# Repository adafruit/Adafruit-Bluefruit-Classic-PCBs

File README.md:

## Bluefruit EZ-Link - Bluetooth Serial Link & Arduino Programmer - v1.3 PCBs (Discontinued)
<a href="http://www.adafruit.com/products/1588"><br/>
Click here to view in the Adafruit shop</a>

The Bluefruit EZ-Link is a regular 'SPP' serial link client device, that can pair with any computer or tablet and appear as a serial/COM port (except iOS as iOS does not permit SPP pairing). But here is where it gets exciting: unlike any other BT module, the EZ-Link can automatically detect and change the serial baud rate. That means if you open up the COM port on your computer at 9600 baud, the output is 9600, 57600? 57600. Yep even 2400. All the most common baud rates are supported: 2400, 4800, 9600, 19200, 38400, 57600, 115200 and 230400. You never have to configure or customize the module by hand - it all happens completely automatically inside the RF module.

PCB files for the discontinued Adafruit Bluefruit Classic (2.1) EZ-Link. The PCB format is EagleCAD schematic and board layout
- https://www.adafruit.com/products/1588

### License

Adafruit invests time and resources providing this open source design, please support Adafruit and open-source hardware by purchasing products from [Adafruit](https://www.adafruit.com)!

All text above must be included in any redistribution

Designed by Limor Fried/Ladyada for Adafruit Industries.
Creative Commons Attribution/Share-Alike, all text above must be included in any redistribution. 
See license.txt for additional information.

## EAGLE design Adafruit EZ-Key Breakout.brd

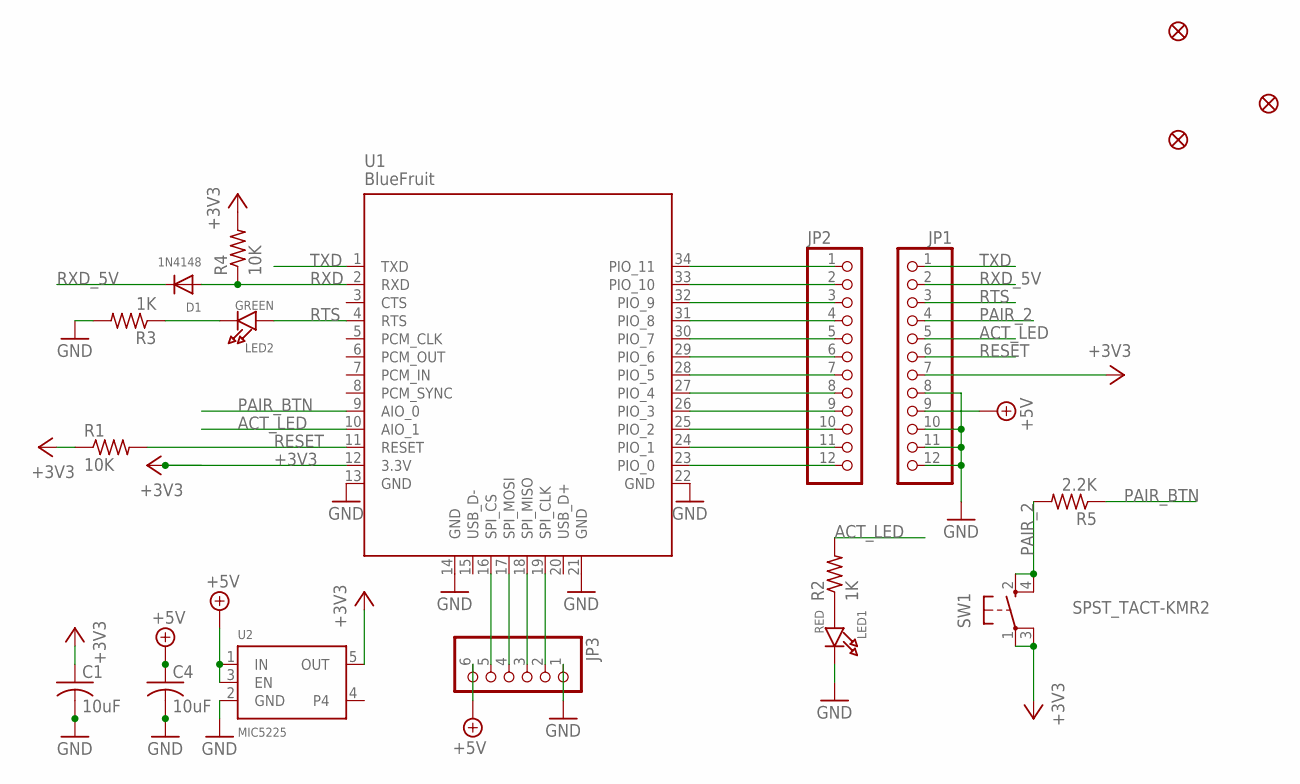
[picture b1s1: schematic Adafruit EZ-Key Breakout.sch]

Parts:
C1, C4: 10uF; C0805
D1: 1N4148; SOD-323
FID1, FID2, FID3: FIDUCIAL""; FIDUCIAL_1MM
JP1, JP2: PINHD-1X12-CB; 1X12-CB
JP3: PINHD-1X6B; 1X06-BIG
LED1: RED; CHIPLED_0805_NOOUTLINE
LED2: GREEN; CHIPLED_0805_NOOUTLINE
R1, R4: 10K; R0805
R2, R3: 1K; R0805
R5: 2.2K; R0805
SW1: SPST_TACT-KMR2; KMR2
U1: BlueFruit; BLUETOOTH_MODULE
U2: MIC5225; SOT23-5

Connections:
+3V3: C1.1, JP1.7, R1.1, R4.2, SW1.1, SW1.3 (P1), U1.12 (3.3V), U2.5 (OUT)
+5V: C4.1, JP1.9, JP3.6, U2.1 (IN), U2.3 (EN)
ACT_LED: JP1.5, R2.2, U1.10 (AIO_1)
CLK: JP3.2, U1.19 (SPI_CLK)
CS: JP3.5, U1.16 (SPI_CS)
GND: C1.2, C4.2, JP1.8, JP1.10, JP1.11, JP1.12, JP3.1, LED1.C, R3.2, U1.13 (GND), U1.14 (GND), U1.21 (GND), U1.22 (GND), U2.2 (GND)
MISO: JP3.3, U1.18 (SPI_MISO)
MOSI: JP3.4, U1.17 (SPI_MOSI)
unnamed: JP2.5, U1.30 (PIO_7)
unnamed: LED1.A, R2.1
unnamed: LED2.C, R3.1
unnamed: JP2.12, U1.23 (PIO_0)
unnamed: JP2.11, U1.24 (PIO_1)
unnamed: JP2.10, U1.25 (PIO_2)
unnamed: JP2.9, U1.26 (PIO_3)
unnamed: JP2.8, U1.27 (PIO_4)
unnamed: JP2.7, U1.28 (PIO_5)
unnamed: JP2.6, U1.29 (PIO_6)
unnamed: JP2.4, U1.31 (PIO_8)
unnamed: JP2.3, U1.32 (PIO_9)
unnamed: JP2.2, U1.33 (PIO_10)
unnamed: JP2.1, U1.34 (PIO_11)
PAIR_2: JP1.4, R5.2, SW1.2 (S), SW1.4 (S1)
PAIR_BTN: R5.1, U1.9 (AIO_0)
RESET: JP1.6, R1.2, U1.11 (RESET)
RTS: JP1.3, LED2.A, U1.4 (RTS)
RXD: D1.A, R4.1, U1.2 (RXD)
RXD_5V: D1.C, JP1.2
TXD: JP1.1, U1.1 (TXD)

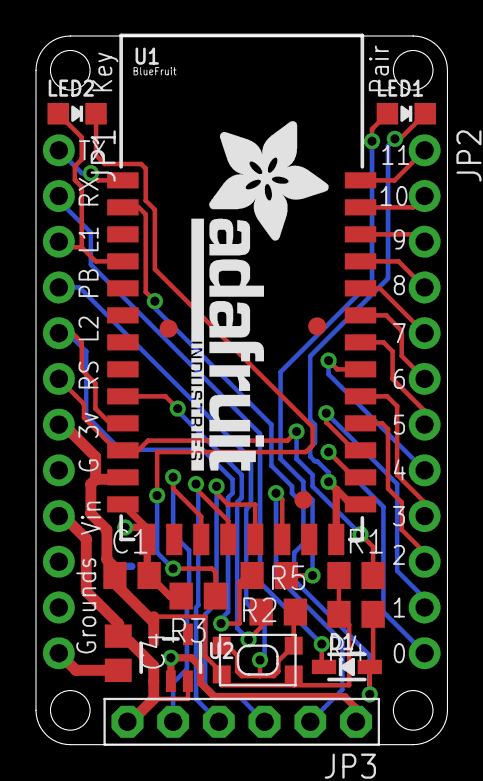
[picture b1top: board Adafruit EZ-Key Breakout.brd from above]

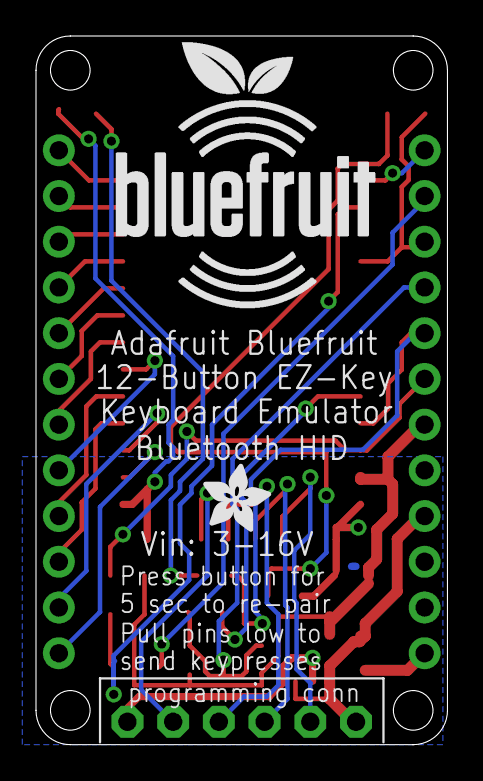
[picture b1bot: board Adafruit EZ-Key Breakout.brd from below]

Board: 2 copper layers, 22.9 x 39.4 mm, 22 parts (2 on the bottom side), 29 nets.

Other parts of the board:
U$2: BLUEFRUITLOGO_150MM
U$3: ADAFRUIT_3.5MM
U$4: ADAFRUIT_TEXT_20MM

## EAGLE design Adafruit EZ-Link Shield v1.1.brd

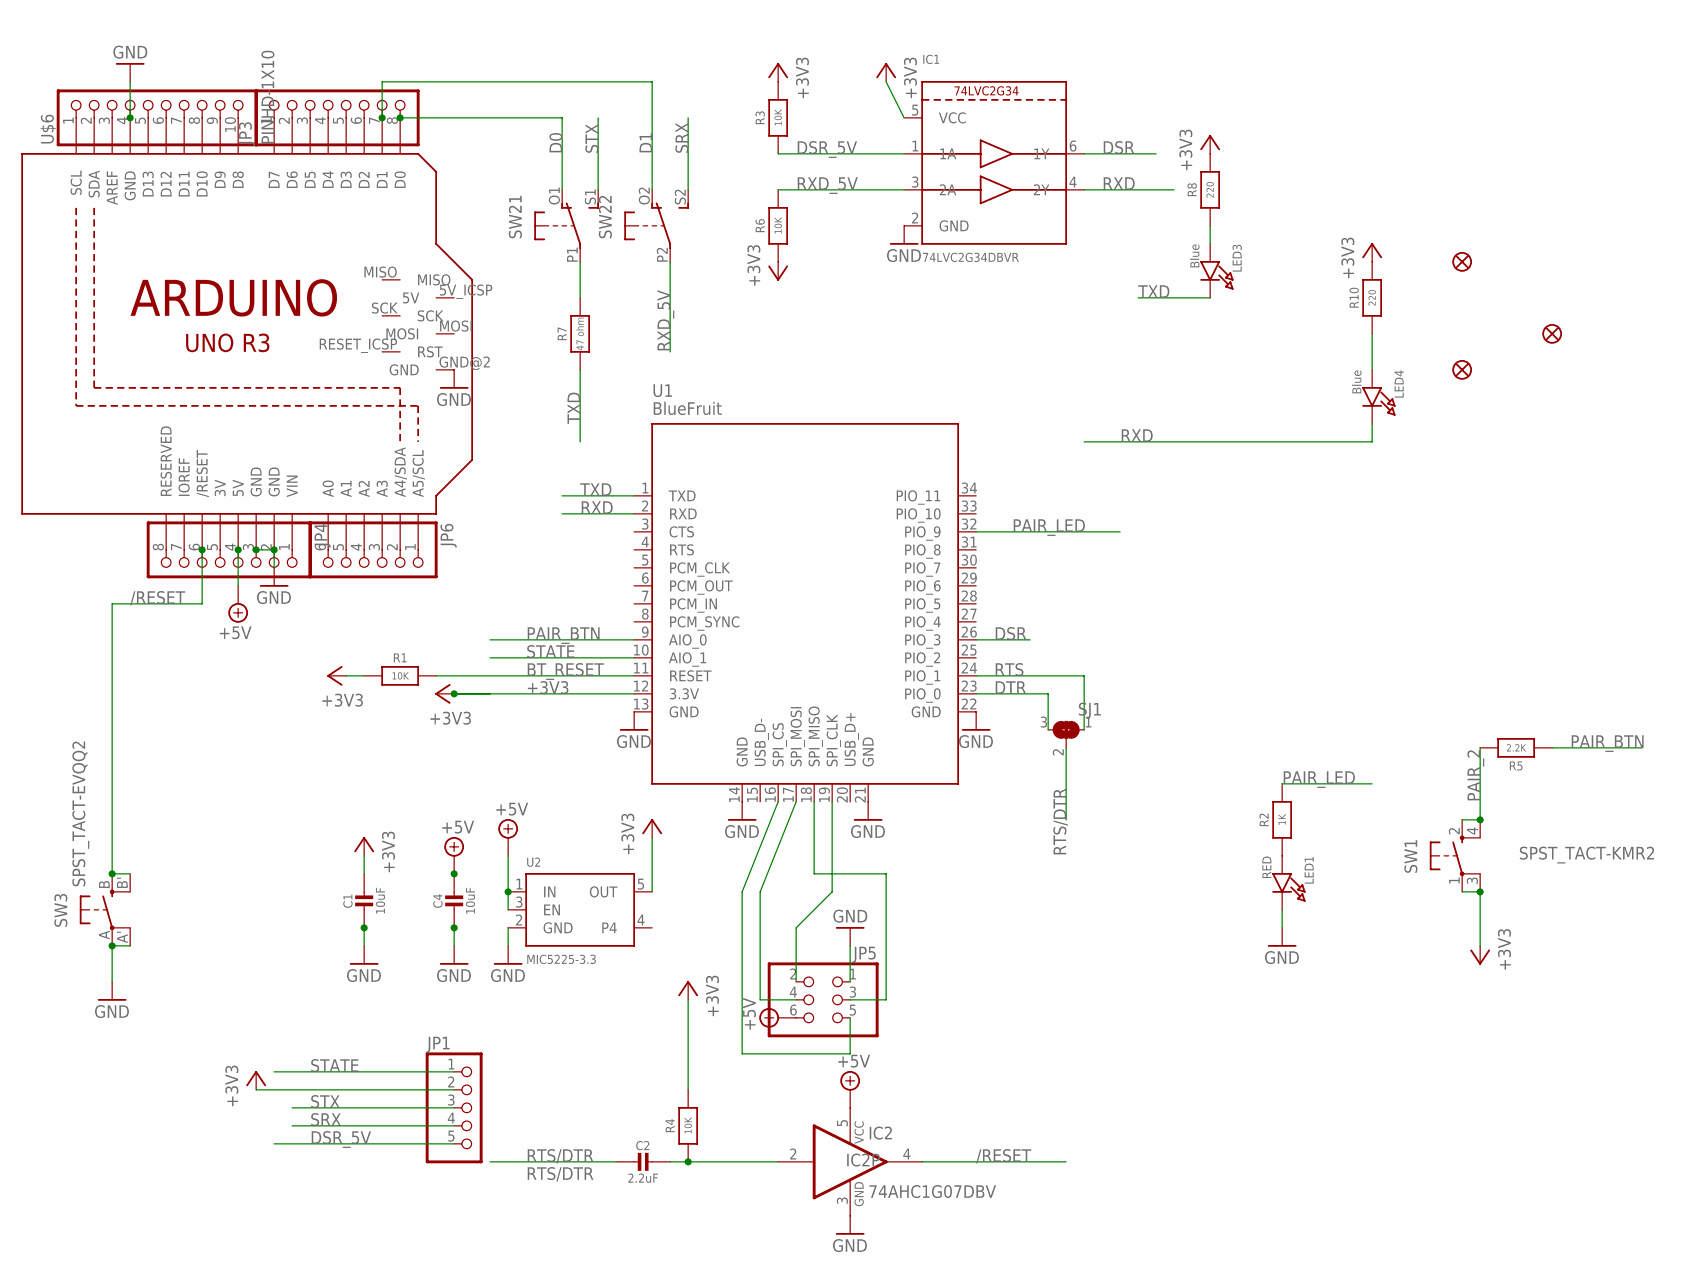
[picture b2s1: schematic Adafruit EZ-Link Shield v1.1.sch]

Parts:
C1, C4: 10uF; 0805-NO
C2: 2.2uF; 0805-NO
FID1, FID2, FID3: FIDUCIAL""; FIDUCIAL_1MM
IC1: 74LVC2G34DBVR; SOT23-6
IC2: 74AHC1G07DBV; SOT23-5
JP1: HEADER-1X570MIL; 1X05_ROUND_70
JP3, JP4: PINHD-1X8BIG; 1X08-BIG
JP5: HEADER-2X3; 2X03_ROUND_70MIL
JP6: PINHD-1X6B; 1X06-BIG
LED1: RED; CHIPLED_0805_NOOUTLINE
LED3, LED4: Blue; CHIPLED_0805_NOOUTLINE
R1, R4: 10K; 0805-NO
R2: 1K; 0805-NO
R3, R6: 10K; _0805MP
R5: 2.2K; 0805-NO
R7: 47 ohm; 0805-NO
R8, R10: 220; 0805-NO
SJ1: SOLDERJUMPER_2WAY; SOLDERJUMPER_2WAY_OPEN_NOPASTE
SW1: SPST_TACT-KMR2; KMR2
SW2: DPDT-EG1390; EG1390
SW3: SPST_TACT-EVQQ2; EVQ-Q2
U1: BlueFruit; BLUETOOTH_MODULE
U2: MIC5225-3.3; SOT23-5
U$5: ARDUINO_R3_ICSP; ARDUINOR3_ICSP
U$6: PINHD-1X10; 1X10-BIG

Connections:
+3V3: C1.1, IC1.5 (VCC), JP1.2, R1.1, R3.2, R4.2, R6.1, R8.2, R10.2, SW1.1, SW1.3 (P1), U1.12 (3.3V), U2.5 (OUT)
+5V: C4.1, IC2.5 (VCC), JP4.4, JP5.6, U2.1 (IN), U2.3 (EN), U$5.5V
/RESET: IC2.4 (O), JP4.6, SW3.B (S), SW3.B' (S1), U$5.RESET (/RESET)
BT_RESET: R1.2, U1.11 (RESET)
D0: JP3.8, SW2.O1 (O), U$5.D0
D1: JP3.7, SW2.O2 (O), U$5.D1
DSR: IC1.6 (1Y), U1.26 (PIO_3)
DSR_5V: IC1.1 (1A), JP1.5, R3.1
DTR: SJ1.3, U1.23 (PIO_0)
GND: C1.2, C4.2, IC1.2 (GND), IC2.3 (GND), JP4.2, JP4.3, JP5.1, LED1.C, SW3.A, SW3.A' (P1), U1.13 (GND), U1.14 (GND), U1.21 (GND), U1.22 (GND), U2.2 (GND), U$5.GND, U$5.GND@1 (GND), U$5.GND@2 (GND), U$5.GND@3 (GND), U$6.4
unnamed: C2.1, IC2.2 (I), R4.1
unnamed: LED1.A, R2.1
unnamed: R7.2, SW2.P1
unnamed: JP3.1, U$5.D7
unnamed: JP3.2, U$5.D6
unnamed: LED3.A, R8.1
unnamed: JP3.3, U$5.D5
unnamed: JP3.4, U$5.D4
unnamed: LED4.A, R10.1
unnamed: JP3.5, U$5.D3
unnamed: JP3.6, U$5.D2
unnamed: JP4.1, U$5.VIN
unnamed: JP4.5, U$5.3V
unnamed: JP4.7, U$5.IOREF
unnamed: JP4.8, U$5.RESERVED
unnamed: JP6.1, U$5.A5 (A5/SCL)
unnamed: JP6.2, U$5.A4 (A4/SDA)
unnamed: JP6.3, U$5.A3
unnamed: JP6.4, U$5.A2
unnamed: JP6.5, U$5.A1
unnamed: JP6.6, U$5.A0
unnamed: U$5.SCL, U$6.1
unnamed: U$5.SDA, U$6.2
unnamed: U$5.AREF, U$6.3
unnamed: U$5.D13, U$6.5
unnamed: U$5.D12, U$6.6
unnamed: U$5.D11, U$6.7
unnamed: U$5.D10, U$6.8
unnamed: U$5.D9, U$6.9
unnamed: U$5.D8, U$6.10
PAIR_2: R5.2, SW1.2 (S), SW1.4 (S1)
PAIR_BTN: R5.1, U1.9 (AIO_0)
PAIR_LED: R2.2, U1.32 (PIO_9)
RTS: SJ1.1, U1.24 (PIO_1)
RTS/DTR: C2.2, SJ1.2
RXD: IC1.4 (2Y), LED4.C, U1.2 (RXD)
RXD_5V: IC1.3 (2A), R6.2, SW2.P2
SPI_CLK: JP5.2, U1.19 (SPI_CLK)
SPI_CS: JP5.5, U1.16 (SPI_CS)
SPI_MISO: JP5.3, U1.18 (SPI_MISO)
SPI_MOSI: JP5.4, U1.17 (SPI_MOSI)
SRX: JP1.4, SW2.S2 (S)
STATE: JP1.1, U1.10 (AIO_1)
STX: JP1.3, SW2.S1 (S)
TXD: LED3.C, R7.1, U1.1 (TXD)

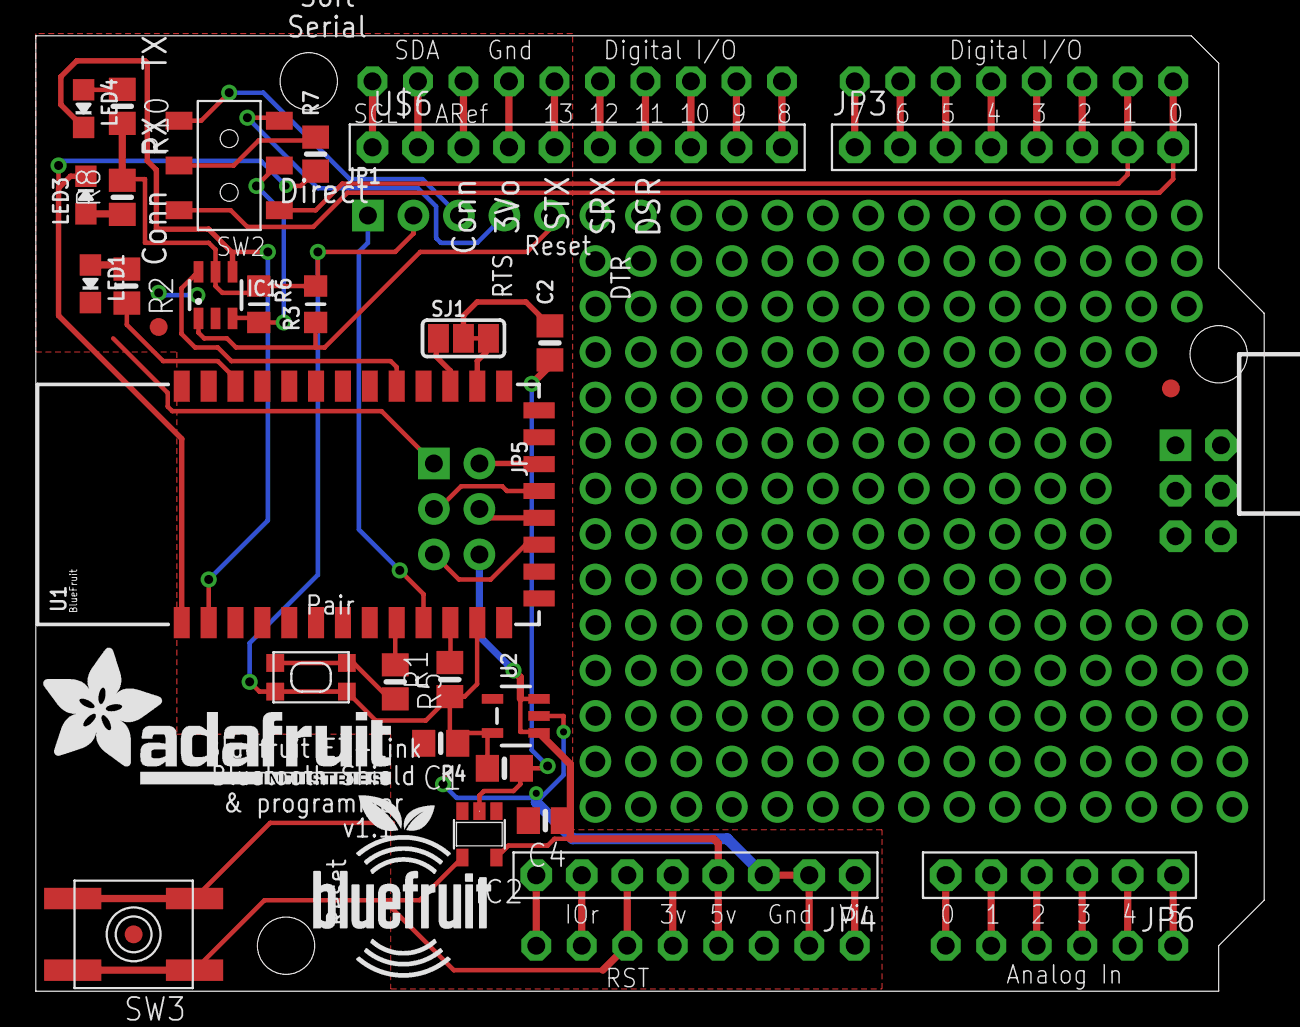
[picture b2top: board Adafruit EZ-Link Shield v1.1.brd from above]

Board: 2 copper layers, 68.6 x 53.3 mm, 35 parts (0 on the bottom side), 55 nets.

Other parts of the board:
U$4: BLUEFRUITLOGO_100MM
U$7: ADAFRUIT_TEXT_20MM

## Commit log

2014-05-14 the EZ-series PCBs
2014-05-14 readme urls
2016-09-21 just ez-link
